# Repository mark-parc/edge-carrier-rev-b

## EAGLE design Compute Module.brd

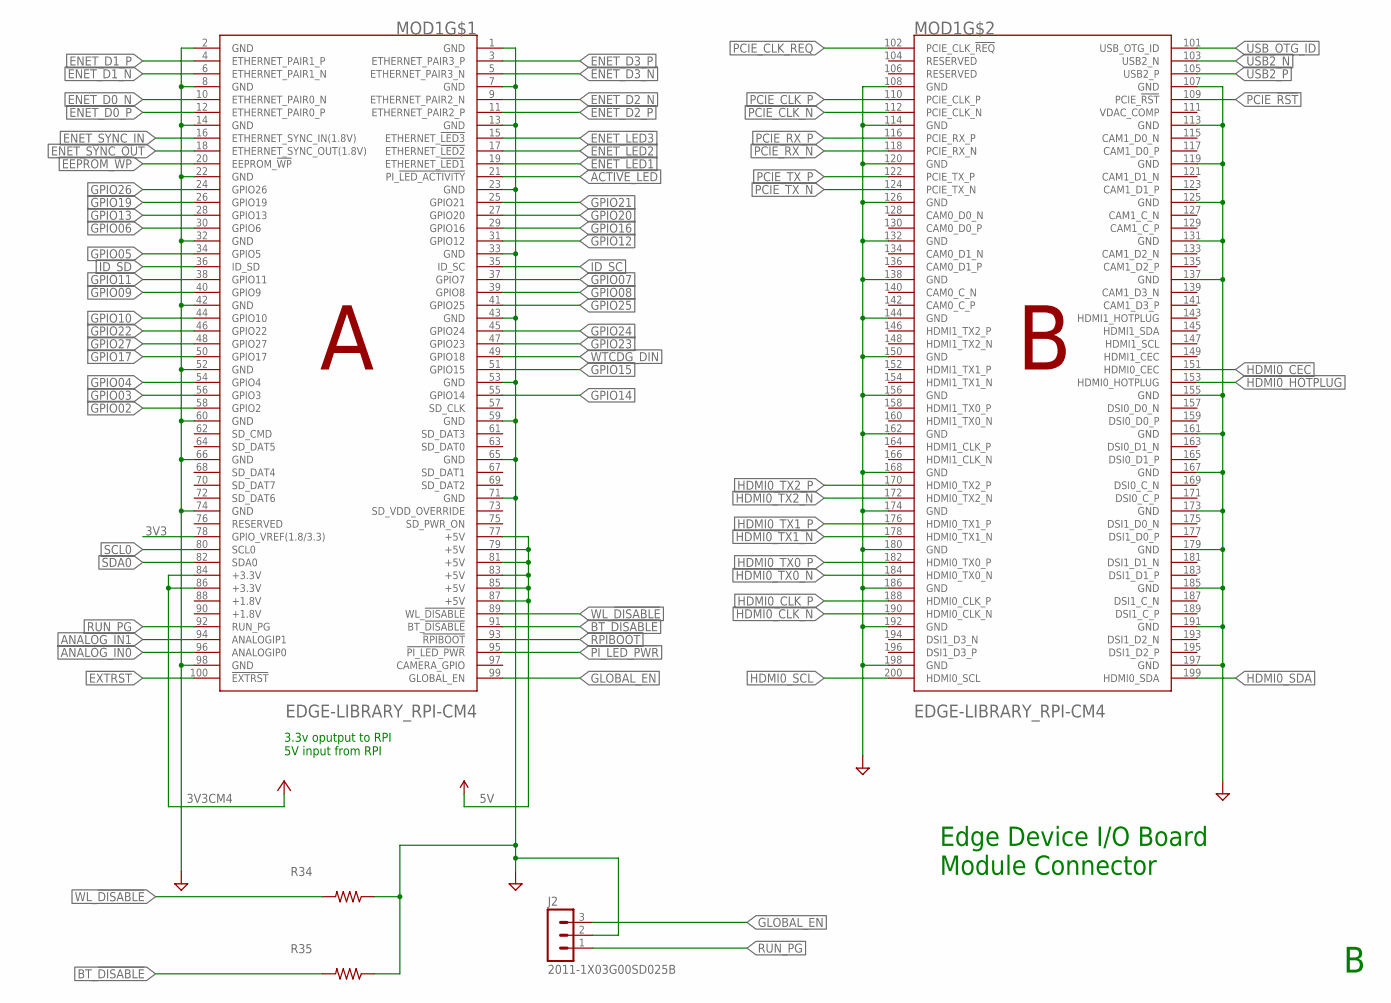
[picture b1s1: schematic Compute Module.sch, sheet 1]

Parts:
J2: 2011-1X03G00SD025B; CON-LSTB_MA03-1; MPN 2011-1X03G00SB; DIGIKEY 2553-2011-1X03G00SB-ND
MOD1: EDGE-LIBRARY_RPI-CM4
R34, R35: EDGE-LIBRARY_0805; MPN RC0805JR-070RL; DIGIKEY 311-0.0ARCT-ND

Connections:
3V3: MOD1.78 (GPIO_VREF(1.8/3.3)); also elsewhere on the board
3V3CM4: MOD1.84 (+3.3V), MOD1.86 (+3.3V)
5V: MOD1.77 (+5V), MOD1.79 (+5V), MOD1.81 (+5V), MOD1.83 (+5V), MOD1.85 (+5V), MOD1.87 (+5V); also elsewhere on the board
!EXTRST: MOD1.100 (!EXTRST); also elsewhere on the board
!PI_LED_PWR: MOD1.95 (!PI_LED_PWR); also elsewhere on the board
!RPIBOOT: MOD1.93 (!RPIBOOT); also elsewhere on the board
ACTIVE_!LED: MOD1.21 (PI_!LED_ACTIVITY); also elsewhere on the board
ANALOG_IN0: MOD1.96 (ANALOGIP0); also elsewhere on the board
ANALOG_IN1: MOD1.94 (ANALOGIP1); also elsewhere on the board
BT_!DISABLE: MOD1.91 (BT_!DISABLE), R35.2
EEPROM_!WP: MOD1.20 (EEPROM_!WP); also elsewhere on the board
ENET_!LED1: MOD1.19 (ETHERNET_!LED1); also elsewhere on the board
ENET_!LED2: MOD1.17 (ETHERNET_!LED2); also elsewhere on the board
ENET_!LED3: MOD1.15 (ETHERNET_!LED3); also elsewhere on the board
ENET_D0_N: MOD1.10 (ETHERNET_PAIR0_N); also elsewhere on the board
ENET_D0_P: MOD1.12 (ETHERNET_PAIR0_P); also elsewhere on the board
ENET_D1_N: MOD1.6 (ETHERNET_PAIR1_N); also elsewhere on the board
ENET_D1_P: MOD1.4 (ETHERNET_PAIR1_P); also elsewhere on the board
ENET_D2_N: MOD1.9 (ETHERNET_PAIR2_N); also elsewhere on the board
ENET_D2_P: MOD1.11 (ETHERNET_PAIR2_P); also elsewhere on the board
ENET_D3_N: MOD1.5 (ETHERNET_PAIR3_N); also elsewhere on the board
ENET_D3_P: MOD1.3 (ETHERNET_PAIR3_P); also elsewhere on the board
ENET_SYNC_IN: MOD1.16 (ETHERNET_SYNC_IN(1.8V)); also elsewhere on the board
ENET_SYNC_OUT: MOD1.18 (ETHERNET_SYNC_OUT(1.8V)); also elsewhere on the board
GLOBAL_EN: J2.3, MOD1.99 (GLOBAL_EN); also elsewhere on the board
GND: J2.2, MOD1.1 (GND), MOD1.2 (GND), MOD1.7 (GND), MOD1.8 (GND), MOD1.13 (GND), MOD1.14 (GND), MOD1.22 (GND), MOD1.23 (GND), MOD1.32 (GND), MOD1.33 (GND), MOD1.42 (GND), MOD1.43 (GND), MOD1.52 (GND), MOD1.53 (GND), MOD1.59 (GND), MOD1.60 (GND), MOD1.65 (GND), MOD1.66 (GND), MOD1.71 (GND), MOD1.74 (GND), MOD1.98 (GND), MOD1.107 (GND), MOD1.108 (GND), MOD1.113 (GND), MOD1.114 (GND), MOD1.119 (GND), MOD1.120 (GND), MOD1.125 (GND), MOD1.126 (GND), MOD1.131 (GND), MOD1.132 (GND), MOD1.137 (GND), MOD1.138 (GND), MOD1.144 (GND), MOD1.150 (GND), MOD1.155 (GND), MOD1.156 (GND), MOD1.161 (GND), MOD1.162 (GND), MOD1.167 (GND), MOD1.168 (GND), MOD1.173 (GND), MOD1.174 (GND), MOD1.179 (GND), MOD1.180 (GND), MOD1.185 (GND), MOD1.186 (GND), MOD1.191 (GND), MOD1.192 (GND), MOD1.197 (GND), MOD1.198 (GND), R34.1, R35.1; also elsewhere on the board
GPIO02: MOD1.58 (GPIO2); also elsewhere on the board
GPIO03: MOD1.56 (GPIO3); also elsewhere on the board
GPIO04: MOD1.54 (GPIO4); also elsewhere on the board
GPIO05: MOD1.34 (GPIO5); also elsewhere on the board
GPIO06: MOD1.30 (GPIO6); also elsewhere on the board
GPIO07: MOD1.37 (GPIO7); also elsewhere on the board
GPIO08: MOD1.39 (GPIO8); also elsewhere on the board
GPIO09: MOD1.40 (GPIO9); also elsewhere on the board
GPIO10: MOD1.44 (GPIO10); also elsewhere on the board
GPIO11: MOD1.38 (GPIO11); also elsewhere on the board
GPIO12: MOD1.31 (GPIO12); also elsewhere on the board
GPIO13: MOD1.28 (GPIO13); also elsewhere on the board
GPIO14: MOD1.55 (GPIO14); also elsewhere on the board
GPIO15: MOD1.51 (GPIO15); also elsewhere on the board
GPIO16: MOD1.29 (GPIO16); also elsewhere on the board
GPIO17: MOD1.50 (GPIO17); also elsewhere on the board
GPIO19: MOD1.26 (GPIO19); also elsewhere on the board
GPIO20: MOD1.27 (GPIO20); also elsewhere on the board
GPIO21: MOD1.25 (GPIO21); also elsewhere on the board
GPIO22: MOD1.46 (GPIO22); also elsewhere on the board
GPIO23: MOD1.47 (GPIO23); also elsewhere on the board
GPIO24: MOD1.45 (GPIO24); also elsewhere on the board
GPIO25: MOD1.41 (GPIO25); also elsewhere on the board
GPIO26: MOD1.24 (GPIO26); also elsewhere on the board
GPIO27: MOD1.48 (GPIO27); also elsewhere on the board
HDMI0_CEC: MOD1.151 (HDMI0_CEC); also elsewhere on the board
HDMI0_CLK_N: MOD1.190 (HDMI0_CLK_N); also elsewhere on the board
HDMI0_CLK_P: MOD1.188 (HDMI0_CLK_P); also elsewhere on the board
HDMI0_HOTPLUG: MOD1.153 (HDMI0_HOTPLUG); also elsewhere on the board
HDMI0_SCL: MOD1.200 (HDMI0_SCL); also elsewhere on the board
HDMI0_SDA: MOD1.199 (HDMI0_SDA); also elsewhere on the board
HDMI0_TX0_N: MOD1.184 (HDMI0_TX0_N); also elsewhere on the board
HDMI0_TX0_P: MOD1.182 (HDMI0_TX0_P); also elsewhere on the board
HDMI0_TX1_N: MOD1.178 (HDMI0_TX1_N); also elsewhere on the board
HDMI0_TX1_P: MOD1.176 (HDMI0_TX1_P); also elsewhere on the board
HDMI0_TX2_N: MOD1.172 (HDMI0_TX2_N); also elsewhere on the board
HDMI0_TX2_P: MOD1.170 (HDMI0_TX2_P); also elsewhere on the board
ID_SC: MOD1.35 (ID_SC); also elsewhere on the board
ID_SD: MOD1.36 (ID_SD); also elsewhere on the board
PCIE_!RST: MOD1.109 (PCIE_!RST); also elsewhere on the board
PCIE_CLK_!REQ: MOD1.102 (PCIE_CLK_!REQ); also elsewhere on the board
PCIE_CLK_N: MOD1.112 (PCIE_CLK_N); also elsewhere on the board
PCIE_CLK_P: MOD1.110 (PCIE_CLK_P); also elsewhere on the board
PCIE_RX_N: MOD1.118 (PCIE_RX_N); also elsewhere on the board
PCIE_RX_P: MOD1.116 (PCIE_RX_P); also elsewhere on the board
PCIE_TX_N: MOD1.124 (PCIE_TX_N); also elsewhere on the board
PCIE_TX_P: MOD1.122 (PCIE_TX_P); also elsewhere on the board
RUN_PG: J2.1, MOD1.92 (RUN_PG); also elsewhere on the board
SCL0: MOD1.80 (SCL0); also elsewhere on the board
SDA0: MOD1.82 (SDA0); also elsewhere on the board
USB2_N: MOD1.103 (USB2_N); also elsewhere on the board
USB2_P: MOD1.105 (USB2_P); also elsewhere on the board
USB_OTG_ID: MOD1.101 (USB_OTG_ID); also elsewhere on the board
WL_!DISABLE: MOD1.89 (WL_!DISABLE), R34.2
WTCDG_DIN: MOD1.49 (GPIO18); also elsewhere on the board

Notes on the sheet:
Edge Device I/O Board Module Connector
3.3v oputput to RPI 5V input from RPI

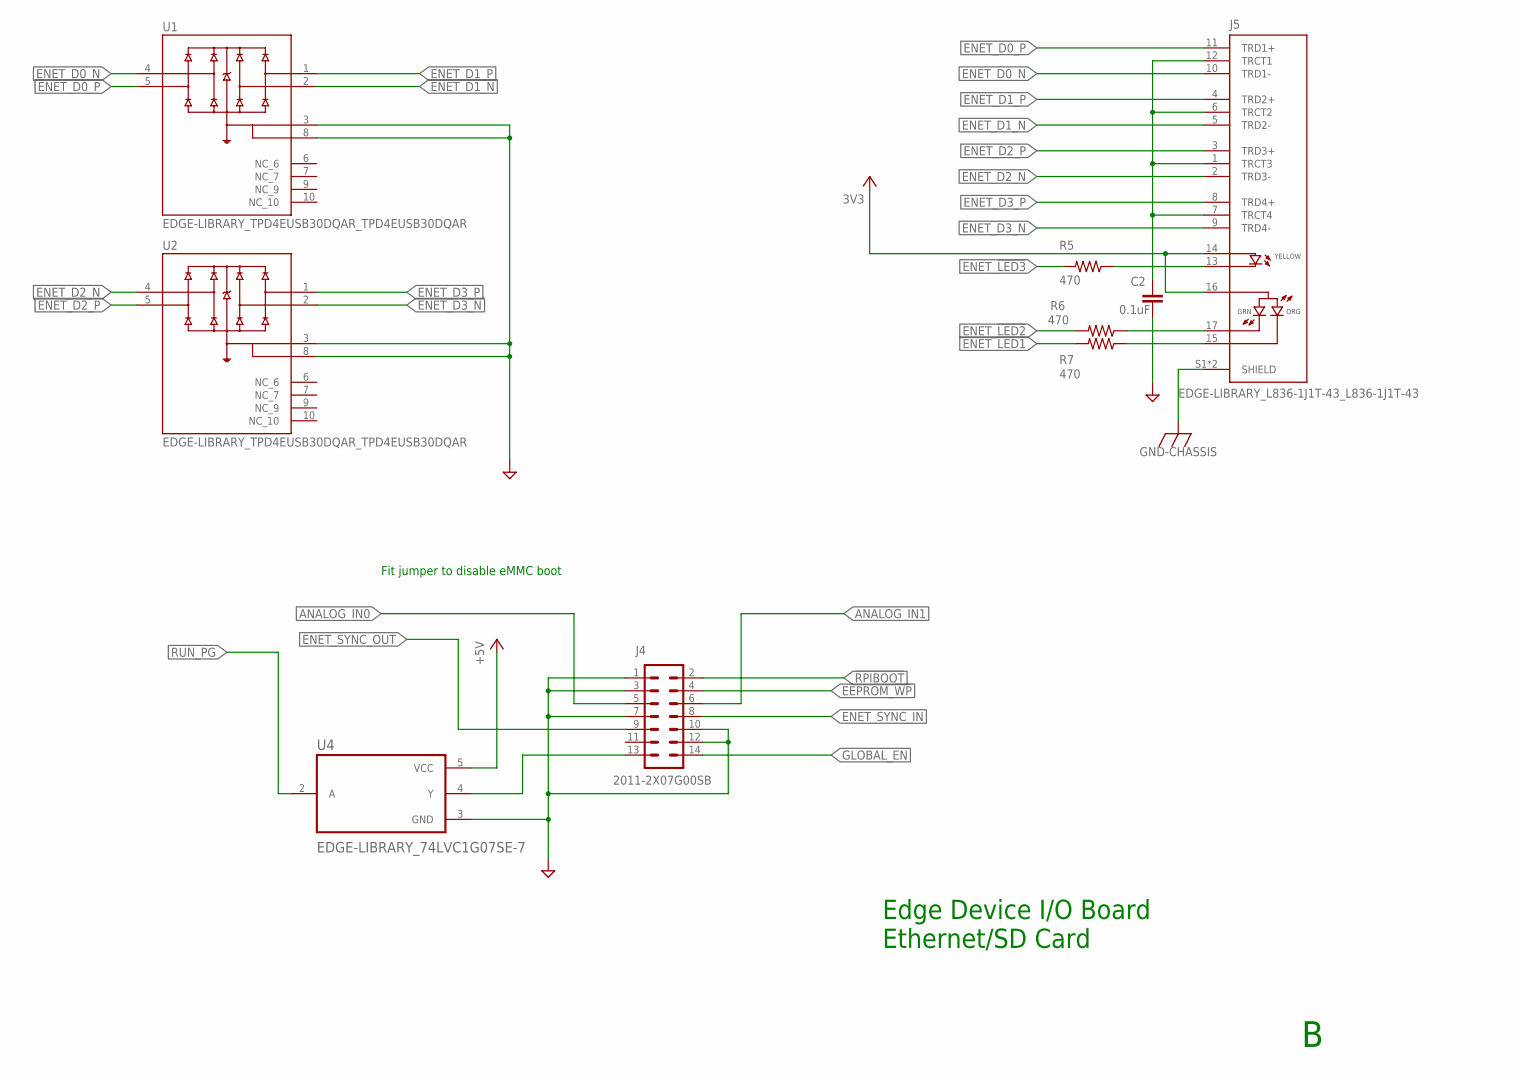
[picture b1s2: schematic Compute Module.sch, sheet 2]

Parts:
C2: 0.1uF; EDGE-LIBRARY_TUTORIAL---FUSION-360_CAPC1005X60; MPN C0402C104K4RACTU; DIGIKEY 399-3521-1-ND
J4: 2011-2X07G00SB; CON-LSTB_MA07-2; MPN 2011-2X07G00SB; DIGIKEY 2553-2011-2X07G00SB-ND
J5: EDGE-LIBRARY_L836-1J1T-43_L836-1J1T-43; EDGE-LIBRARY_L836-1J1T-43_BEL_L836-1J1T-43
R5, R6, R7: 470; EDGE-LIBRARY_TUTORIAL---FUSION-360_RESC1005X40; MPN RC0402FR-07470RL; DIGIKEY 311-470LRCT-ND
U1, U2: EDGE-LIBRARY_TPD4EUSB30DQAR_TPD4EUSB30DQAR; EDGE-LIBRARY_TPD4EUSB30DQAR_IC_TPD4EUSB30DQAR
U4: EDGE-LIBRARY_74LVC1G07SE-7; EDGE-LIBRARY_SOT65P210X110-5N

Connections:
3V3: J5.14, J5.16; also elsewhere on the board
5V: U4.5 (VCC); also elsewhere on the board
!RPIBOOT: J4.2; also elsewhere on the board
ANALOG_IN0: J4.5; also elsewhere on the board
ANALOG_IN1: J4.6; also elsewhere on the board
CGND: J5.S1 (SHIELD), J5.S2 (SHIELD); also elsewhere on the board
EEPROM_!WP: J4.4; also elsewhere on the board
ENET_!LED1: R7.2; also elsewhere on the board
ENET_!LED2: R6.2; also elsewhere on the board
ENET_!LED3: R5.2; also elsewhere on the board
ENET_D0_N: J5.10 (TRD1-), U1.4 (D2+); also elsewhere on the board
ENET_D0_P: J5.11 (TRD1+), U1.5 (D2-); also elsewhere on the board
ENET_D1_N: J5.5 (TRD2-), U1.2 (D1-); also elsewhere on the board
ENET_D1_P: J5.4 (TRD2+), U1.1 (D1+); also elsewhere on the board
ENET_D2_N: J5.2 (TRD3-), U2.4 (D2+); also elsewhere on the board
ENET_D2_P: J5.3 (TRD3+), U2.5 (D2-); also elsewhere on the board
ENET_D3_N: J5.9 (TRD4-), U2.2 (D1-); also elsewhere on the board
ENET_D3_P: J5.8 (TRD4+), U2.1 (D1+); also elsewhere on the board
ENET_SYNC_IN: J4.8; also elsewhere on the board
ENET_SYNC_OUT: J4.9; also elsewhere on the board
GLOBAL_EN: J4.14; also elsewhere on the board
GND: C2.2, J4.1, J4.3, J4.7, J4.10, J4.12, U1.3 (GND_3), U1.8 (GND_8), U2.3 (GND_3), U2.8 (GND_8), U4.3 (GND); also elsewhere on the board
unnamed: C2.1, J5.1 (TRCT3), J5.6 (TRCT2), J5.7 (TRCT4), J5.12 (TRCT1)
unnamed: J5.13, R5.1
unnamed: J5.17, R6.1
unnamed: J5.15, R7.1
unnamed: J4.13, U4.4 (Y)
RUN_PG: U4.2 (A); also elsewhere on the board

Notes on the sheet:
Edge Device I/O Board Ethernet/SD Card
Fit jumper to disable eMMC boot

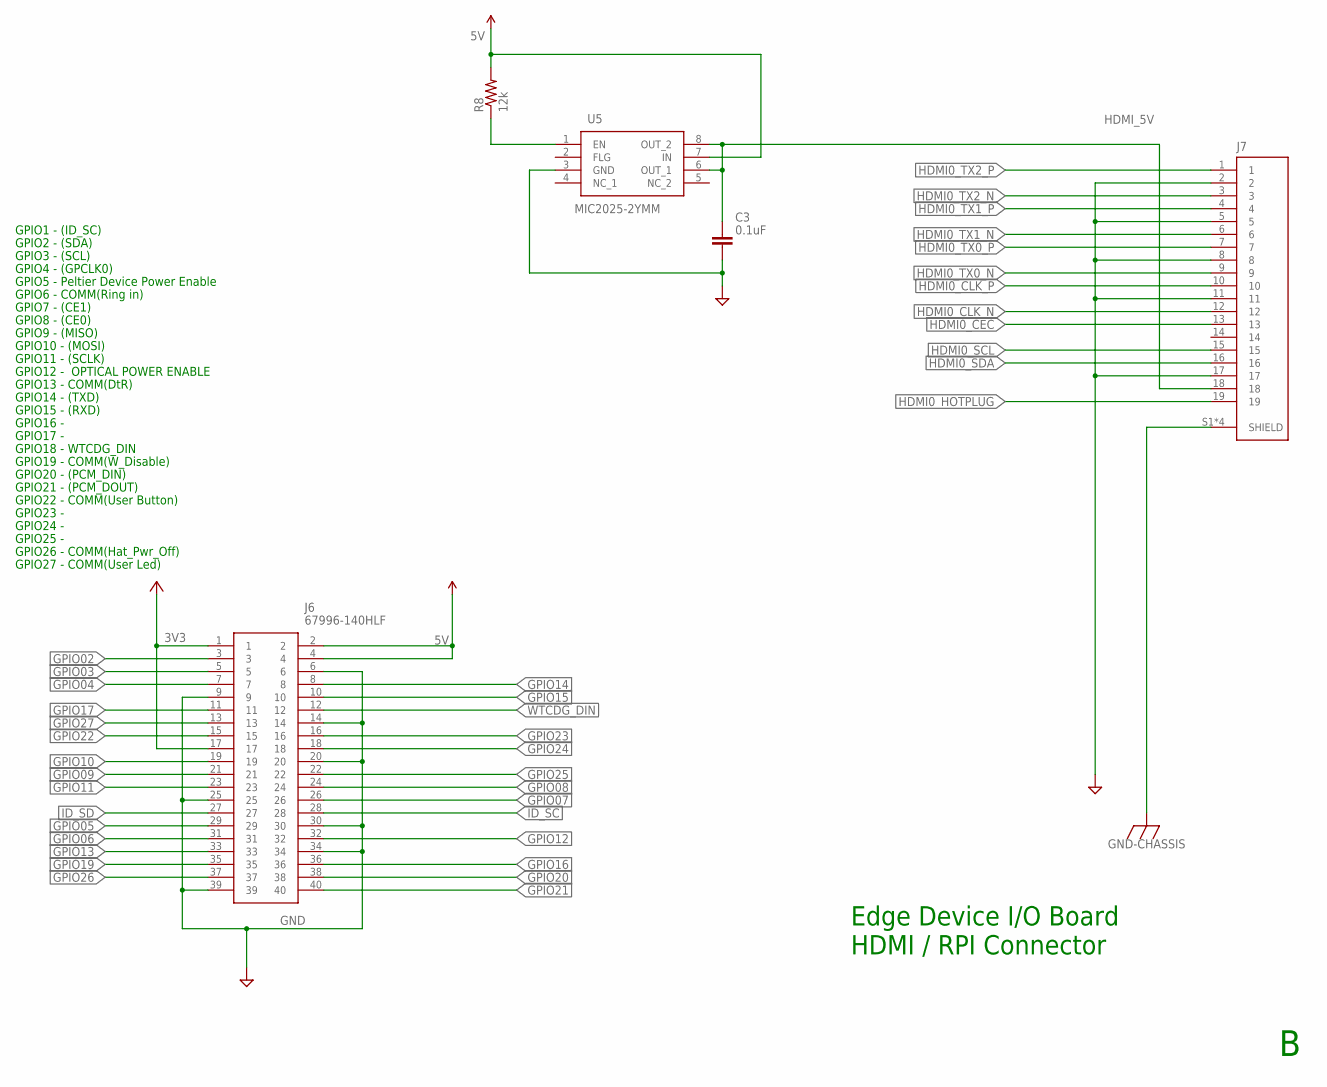
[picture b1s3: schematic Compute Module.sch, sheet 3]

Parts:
C3: 0.1uF; EDGE-LIBRARY_TUTORIAL---FUSION-360_CAPC1005X60; MPN C0402C104K4RACTU; DIGIKEY 399-3521-1-ND
J6: 67996-140HLF; HDRV40W67P254_2X20_5080X483X85
J7: EDGE-LIBRARY_HDMI_CONNECTOR_RT_SMA; EDGE-LIBRARY_STEWART_SS-53000-001
R8: 12k; EDGE-LIBRARY_TUTORIAL---FUSION-360_RESC1005X40; MPN RC0402FR-0712KL; DIGIKEY 311-12.0KLRCT-ND
U5: MIC2025-2YMM; SOP65P490X110-8N

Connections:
3V3: J6.1, J6.17; also elsewhere on the board
5V: J6.2, J6.4, R8.2, U5.7 (IN); also elsewhere on the board
CGND: J7.S1 (SHIELD), J7.S2 (SHIELD), J7.S3 (SHIELD), J7.S4 (SHIELD); also elsewhere on the board
GND: C3.2, J6.6, J6.9, J6.14, J6.20, J6.25, J6.30, J6.34, J6.39, J7.2, J7.5, J7.8, J7.11, J7.17, U5.3 (GND); also elsewhere on the board
GPIO02: J6.3; also elsewhere on the board
GPIO03: J6.5; also elsewhere on the board
GPIO04: J6.7; also elsewhere on the board
GPIO05: J6.29; also elsewhere on the board
GPIO06: J6.31; also elsewhere on the board
GPIO07: J6.26; also elsewhere on the board
GPIO08: J6.24; also elsewhere on the board
GPIO09: J6.21; also elsewhere on the board
GPIO10: J6.19; also elsewhere on the board
GPIO11: J6.23; also elsewhere on the board
GPIO12: J6.32; also elsewhere on the board
GPIO13: J6.33; also elsewhere on the board
GPIO14: J6.8; also elsewhere on the board
GPIO15: J6.10; also elsewhere on the board
GPIO16: J6.36; also elsewhere on the board
GPIO17: J6.11; also elsewhere on the board
GPIO19: J6.35; also elsewhere on the board
GPIO20: J6.38; also elsewhere on the board
GPIO21: J6.40; also elsewhere on the board
GPIO22: J6.15; also elsewhere on the board
GPIO23: J6.16; also elsewhere on the board
GPIO24: J6.18; also elsewhere on the board
GPIO25: J6.22; also elsewhere on the board
GPIO26: J6.37; also elsewhere on the board
GPIO27: J6.13; also elsewhere on the board
HDMI0_CEC: J7.13; also elsewhere on the board
HDMI0_CLK_N: J7.12; also elsewhere on the board
HDMI0_CLK_P: J7.10; also elsewhere on the board
HDMI0_HOTPLUG: J7.19; also elsewhere on the board
HDMI0_SCL: J7.15; also elsewhere on the board
HDMI0_SDA: J7.16; also elsewhere on the board
HDMI0_TX0_N: J7.9; also elsewhere on the board
HDMI0_TX0_P: J7.7; also elsewhere on the board
HDMI0_TX1_N: J7.6; also elsewhere on the board
HDMI0_TX1_P: J7.4; also elsewhere on the board
HDMI0_TX2_N: J7.3; also elsewhere on the board
HDMI0_TX2_P: J7.1; also elsewhere on the board
HDMI_5V: C3.1, J7.18, U5.6 (OUT_1), U5.8 (OUT_2)
ID_SC: J6.28; also elsewhere on the board
ID_SD: J6.27; also elsewhere on the board
unnamed: R8.1, U5.1 (EN)
WTCDG_DIN: J6.12; also elsewhere on the board

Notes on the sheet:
Edge Device I/O Board HDMI / RPI Connector
GPIO18 - WTCDG_DIN
GPIO27 - COMM(User Led)
GPIO22 - COMM(User Button)
GPIO6 - COMM(Ring in)
GPIO13 - COMM(DtR)
GPIO19 - COMM(W_Disable)
GPIO26 - COMM(Hat_Pwr_Off)
GPIO1 - (ID_SC)
GPIO2 - (SDA)
GPIO3 - (SCL)
GPIO4 - (GPCLK0)
GPIO5 - Peltier Device Power Enable
GPIO7 - (CE1)
GPIO8 - (CE0)
GPIO9 - (MISO)
GPIO10 - (MOSI)
GPIO11 - (SCLK)
GPIO12 - OPTICAL POWER ENABLE
GPIO14 - (TXD)
GPIO15 - (RXD)
GPIO16 -
GPIO17 -
GPIO20 - (PCM_DIN)
GPIO21 - (PCM_DOUT)
GPIO23 -
GPIO24 -
GPIO25 -

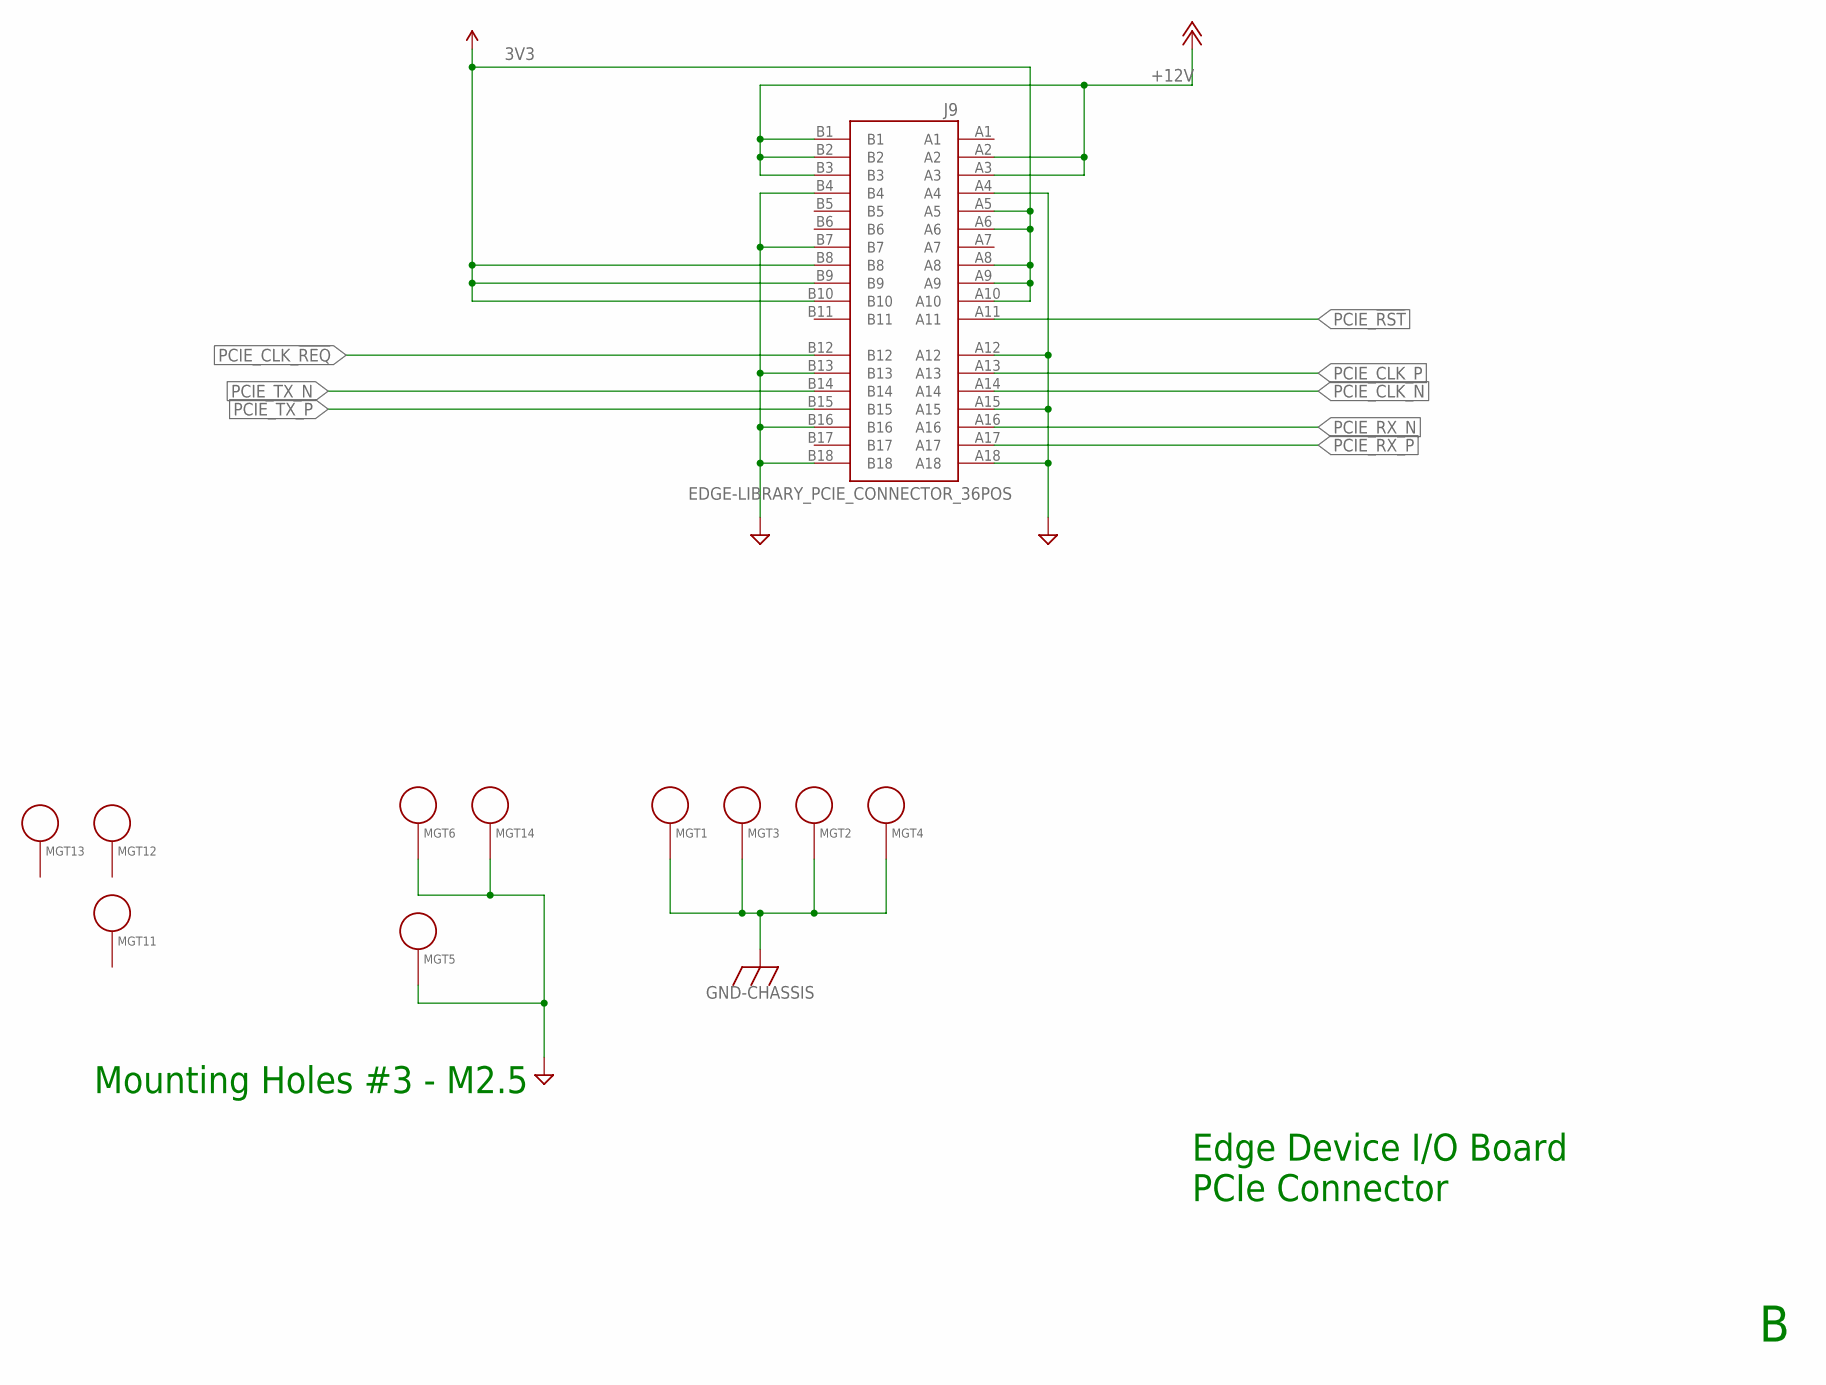
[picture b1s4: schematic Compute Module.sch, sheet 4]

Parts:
J9: EDGE-LIBRARY_PCIE_CONNECTOR_36POS; EDGE-LIBRARY_AMPHENOL_10018784-10210TLF
MGT1, MGT2, MGT3, MGT4, MGT5, MGT6, MGT14: MOUNTING_HOLE; BEAGLEBONEBLACK_MOUNTING_HOLE; DIGIKEY DNP
MGT11, MGT12, MGT13: MOUNTING_HOLE; BEAGLEBONEBLACK_MOUNTING_HOLE

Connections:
3V3: J9.A5, J9.A6, J9.A8, J9.A9, J9.A10, J9.B8, J9.B9, J9.B10; also elsewhere on the board
+12V: J9.A2, J9.A3, J9.B1, J9.B2, J9.B3; also elsewhere on the board
CGND: MGT1.P$1, MGT2.P$1, MGT3.P$1, MGT4.P$1; also elsewhere on the board
GND: J9.A4, J9.A12, J9.A15, J9.A18, J9.B4, J9.B7, J9.B13, J9.B16, J9.B18, MGT5.P$1, MGT6.P$1, MGT14.P$1; also elsewhere on the board
PCIE_!RST: J9.A11; also elsewhere on the board
PCIE_CLK_!REQ: J9.B12; also elsewhere on the board
PCIE_CLK_N: J9.A14; also elsewhere on the board
PCIE_CLK_P: J9.A13; also elsewhere on the board
PCIE_RX_N: J9.A16; also elsewhere on the board
PCIE_RX_P: J9.A17; also elsewhere on the board
PCIE_TX_N: J9.B14; also elsewhere on the board
PCIE_TX_P: J9.B15; also elsewhere on the board

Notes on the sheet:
Edge Device I/O Board PCIe Connector
Mounting Holes #3 - M2.5

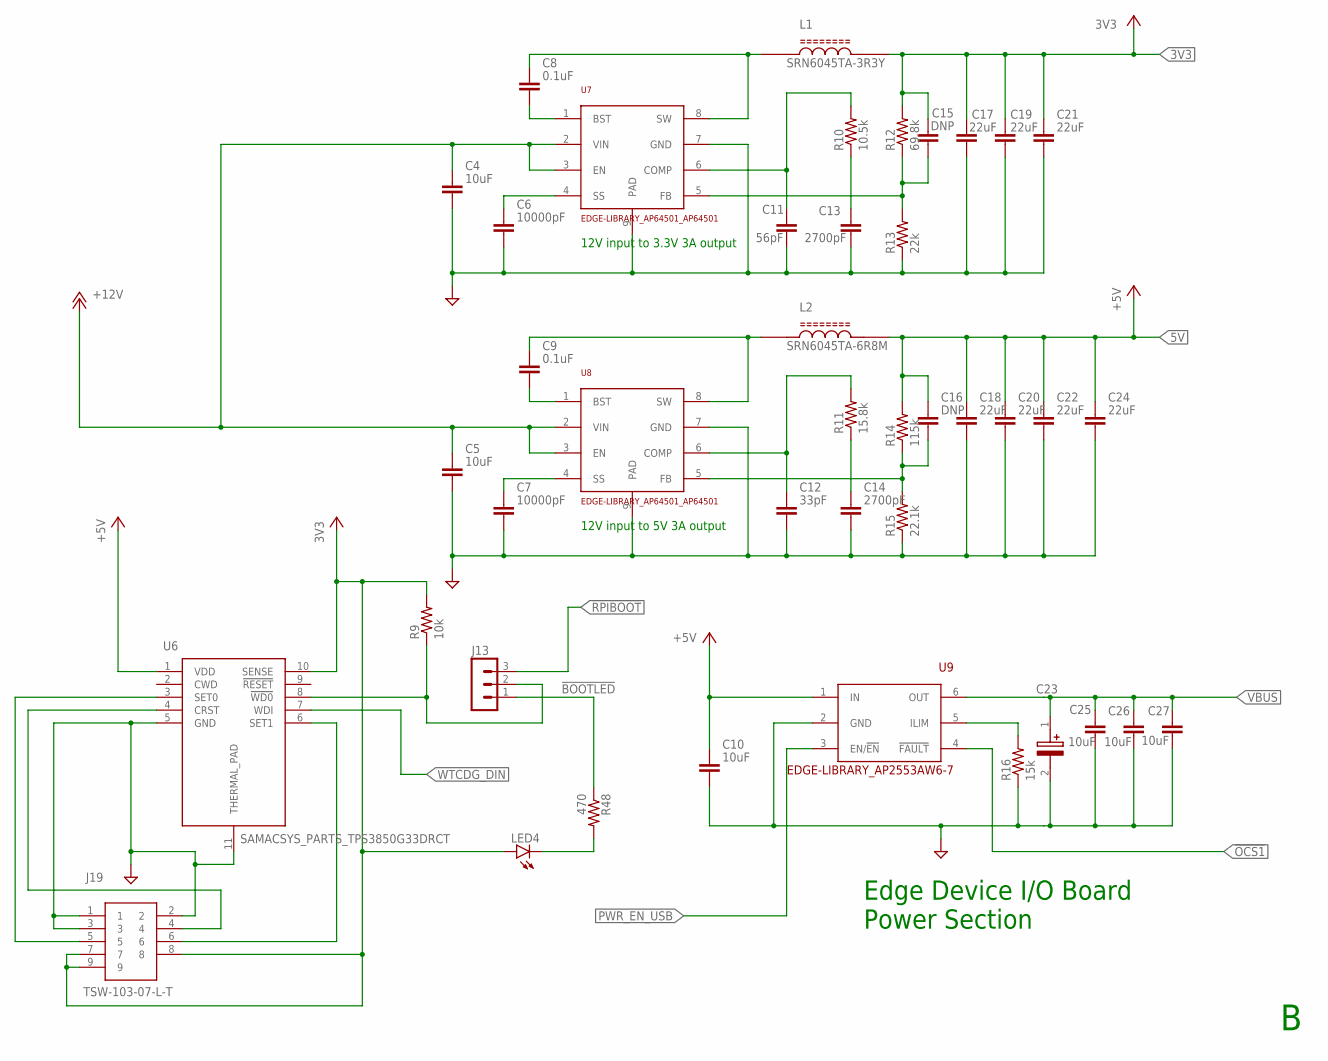
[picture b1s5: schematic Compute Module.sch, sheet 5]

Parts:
C4, C5, C10, C25, C26, C27: 10uF; EDGE-LIBRARY_TUTORIAL---FUSION-360_CAPC2012X110; MPN GRM21BR71A106KA73K; DIGIKEY 490-14381-1-ND
C6, C7: 10000pF; EDGE-LIBRARY_TUTORIAL---FUSION-360_CAPC1005X60; MPN CM02X5R103M16AH; DIGIKEY 1253-CM02X5R103M16AHCT-ND
C8, C9: 0.1uF; EDGE-LIBRARY_TUTORIAL---FUSION-360_CAPC1005X60; MPN C0402C104K4RACTU; DIGIKEY 399-3521-1-ND
C11: 56pF; EDGE-LIBRARY_TUTORIAL---FUSION-360_CAPC1005X60; MPN EMK042CG560JC-W; DIGIKEY 587-6134-1-ND
C12: 33pF; EDGE-LIBRARY_TUTORIAL---FUSION-360_CAPC1005X60; MPN GMC04CG330J16NT; DIGIKEY 2571-GMC04CG330J16NTTR-ND
C13, C14: 2700pF; EDGE-LIBRARY_TUTORIAL---FUSION-360_CAPC1005X60; MPN GMC04X5R272M50NT; DIGIKEY 2571-GMC04X5R272M50NTTR-ND
C15, C16: DNP; EDGE-LIBRARY_TUTORIAL---FUSION-360_CAPC1005X60
C17, C18, C19, C20, C21, C22, C24: 22uF; EDGE-LIBRARY_TUTORIAL---FUSION-360_CAPC1005X60; MPN GMC04X5R226M6R3NT; DIGIKEY 2571-GMC04X5R226M6R3NTTR-ND
C23: 100uF; CAPPM7343X200N
J13: 2553-2011-1X03G00SB-ND; CON-LSTB_MA03-1; MPN 2011-1X03G00SB; DIGIKEY 2553-2011-1X03G00SB-ND
J19: TSW-103-07-L-T; HDRV9W64P254_3X3_762X749X838P
L1: EDGE-LIBRARY_SRN6045TA-3R3Y_SRN6045TA-3R3Y; EDGE-LIBRARY_SRN6045TA-3R3Y_IND_SRN6045TA-3R3Y
L2: EDGE-LIBRARY_SRN6045TA-3R3Y_SRN6045TA-3R3Y; EDGE-LIBRARY_SRN6045TA-3R3Y_IND_SRN6045TA-3R3Y; MPN SRN6045TA-6R8M; DIGIKEY SRN6045TA-6R8MCT-ND
LED4: LTST-S270KGKT; LED_CHIP-LED0603; MPN LTST-S270KGKT; DIGIKEY LTST-S270KGKT
R9: 10k; EDGE-LIBRARY_TUTORIAL---FUSION-360_RESC1005X40; MPN RM04J103CT; DIGIKEY 2571-RM04J103CTTR-ND
R10: 10.5k; EDGE-LIBRARY_TUTORIAL---FUSION-360_RESC1005X40; MPN RC0402FR-0710K5L; DIGIKEY YAG2951CT-ND
R11: 15.8k; EDGE-LIBRARY_TUTORIAL---FUSION-360_RESC1005X40; MPN CRCW040215K8FKED; DIGIKEY 541-15.8KLCT-ND
R12: 69.8k; EDGE-LIBRARY_TUTORIAL---FUSION-360_RESC1005X40; MPN RMCF0402FT69K8; DIGIKEY RMCF0402FT69K8CT-ND
R13: 22k; EDGE-LIBRARY_TUTORIAL---FUSION-360_RESC1005X40; MPN RM04J223CT; DIGIKEY 2571-RM04J222CTTR-ND
R14: 115k; EDGE-LIBRARY_TUTORIAL---FUSION-360_RESC1005X40; MPN RP73PF1E115KBTD; DIGIKEY A127517CT-ND
R15: 22.1k; EDGE-LIBRARY_TUTORIAL---FUSION-360_RESC1005X40; MPN RN04D2212CT10-25; DIGIKEY 2571-RN04D2212CT10-25TR-ND
R16: 15k; EDGE-LIBRARY_TUTORIAL---FUSION-360_RESC1005X40; MPN RMCF0402FT15K0; DIGIKEY RMCF0402FT15K0CT-ND
R48: 470; EDGE-LIBRARY_TUTORIAL---FUSION-360_RESC1005X40; MPN RC0402FR-07470RL; DIGIKEY 311-470LRCT-ND
U6: SAMACSYS_PARTS_TPS3850G33DRCT; SAMACSYS_PARTS_SON50P300X300X100-11N; DIGIKEY 2156-TPS3850G33DRCR-ND
U7, U8: EDGE-LIBRARY_AP64501_AP64501; EDGE-LIBRARY_AP64501_SOIC127P600X265-9T261X350N
U9: EDGE-LIBRARY_AP2553AW6-7; EDGE-LIBRARY_SOT95P280X140-6N; MPN AP22653AW6-7; DIGIKEY 31-AP22653AW6-7CT-ND

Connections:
3V3: C15.1, C17.1, C19.1, C21.1, J19.7, J19.8, J19.9, L1.2, LED4.A, R9.2, R12.2, U6.10 (SENSE); also elsewhere on the board
5V: C10.1, C16.1, C18.1, C20.1, C22.1, C24.1, L2.2, R14.2, U6.1 (VDD), U9.1 (IN); also elsewhere on the board
!BOOTLED: J13.1, R48.1
!OCS1: U9.4 (!FAULT); also elsewhere on the board
!RPIBOOT: J13.3; also elsewhere on the board
+12V: C4.1, C5.1, U7.2 (VIN), U7.3 (EN), U8.2 (VIN), U8.3 (EN); also elsewhere on the board
GND: C4.2, C5.2, C6.2, C7.2, C10.2, C11.2, C12.2, C13.2, C14.2, C17.2, C18.2, C19.2, C20.2, C21.2, C22.2, C23.2 (-), C24.2, C25.2, C26.2, C27.2, J19.1, J19.2, J19.3, R13.1, R15.1, R16.1, U6.5 (GND), U6.11 (THERMAL_PAD), U7.7 (GND), U7.9 (PAD), U8.7 (GND), U8.9 (PAD), U9.2 (GND); also elsewhere on the board
unnamed: J19.6, U6.6 (SET1)
unnamed: C8.2, U7.1 (BST)
unnamed: C8.1, L1.1, U7.8 (SW)
unnamed: C6.1, U7.4 (SS)
unnamed: C11.1, R10.2, U7.6 (COMP)
unnamed: C13.1, R10.1
unnamed: C15.2, R12.1, R13.2, U7.5 (FB)
unnamed: R16.2, U9.5 (ILIM)
unnamed: C9.2, U8.1 (BST)
unnamed: C9.1, L2.1, U8.8 (SW)
unnamed: C7.1, U8.4 (SS)
unnamed: C12.1, R11.2, U8.6 (COMP)
unnamed: C14.1, R11.1
unnamed: C16.2, R14.1, R15.2, U8.5 (FB)
unnamed: J13.2, R9.1, U6.8 (!WD0)
unnamed: LED4.C, R48.2
unnamed: J19.5, U6.3 (SET0)
unnamed: J19.4, U6.4 (CRST)
PWR_EN_USB: U9.3 (EN/!EN); also elsewhere on the board
VBUS: C23.1 (+), C25.1, C26.1, C27.1, U9.6 (OUT); also elsewhere on the board
WTCDG_DIN: U6.7 (WDI); also elsewhere on the board

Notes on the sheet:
12V input to 3.3V 3A output
12V input to 5V 3A output
Edge Device I/O Board Power Section

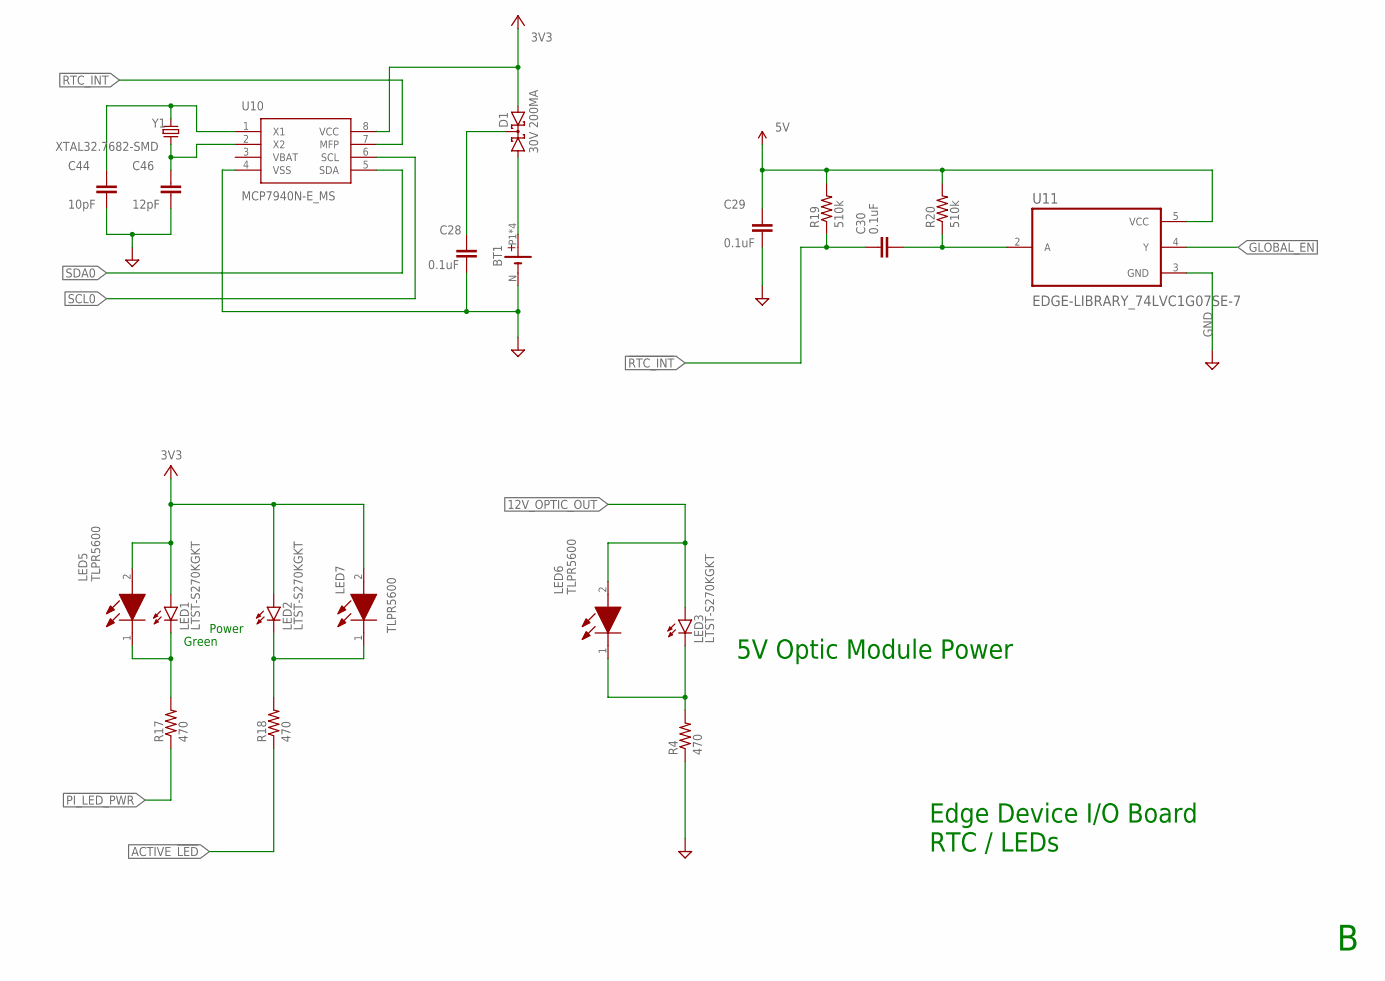
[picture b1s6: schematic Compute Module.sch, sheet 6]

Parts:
BT1: EDGE-LIBRARY_BATTERY_HOLDER; EDGE-LIBRARY_79523141
C28, C29, C30: 0.1uF; EDGE-LIBRARY_TUTORIAL---FUSION-360_CAPC1005X60; MPN C0402C104K4RACTU; DIGIKEY 399-3521-1-ND
C44: 10pF; EDGE-LIBRARY_TUTORIAL---FUSION-360_CAPC1005X60; MPN 478-04026D100JAT2ACT-ND; DIGIKEY 399-3521-1-ND
C46: 12pF; EDGE-LIBRARY_TUTORIAL---FUSION-360_CAPC1005X60; MPN 04026A120KAT2A; DIGIKEY 478-04026A120KAT2ACT-ND
D1: 30V 200MA; EDGE-LIBRARY_SOT23
LED1, LED2, LED3: LTST-S270KGKT; LED_CHIP-LED0603; MPN LTST-S270KGKT; DIGIKEY LTST-S270KGKT
LED5, LED6, LED7: TLPR5600; TLPP5600; DIGIKEY DNP
R4, R17, R18: 470; EDGE-LIBRARY_TUTORIAL---FUSION-360_RESC1005X40; MPN RC0402FR-07470RL; DIGIKEY 311-470LRCT-ND
R19, R20: 510k; EDGE-LIBRARY_TUTORIAL---FUSION-360_RESC1005X40; MPN RMCF0402JT510K; DIGIKEY RMCF0402JT510KCT-ND
U10: MCP7940N-E_MS; SOP65P490X110-8N
U11: EDGE-LIBRARY_74LVC1G07SE-7; EDGE-LIBRARY_SOT65P210X110-5N
Y1: XTAL32.7682-SMD; XTAL_ECS-.327-12.5-34R-TR; MPN QT3C-32.768KDZY-T; DIGIKEY 3003-QT3C-32.768KDZY-T-ND

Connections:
3V3: D1.2 (A2), LED1.A, LED2.A, LED5.2 (A), LED7.2 (A), U10.8 (VCC); also elsewhere on the board
5V: C29.1, R19.2, R20.2, U11.5 (VCC); also elsewhere on the board
12V_OPTIC_OUT: LED3.A, LED6.2 (A); also elsewhere on the board
!PI_LED_PWR: R17.1; also elsewhere on the board
!RTC_INT: C30.1, R19.1, U10.7 (MFP)
ACTIVE_!LED: R18.1; also elsewhere on the board
GLOBAL_EN: U11.4 (Y); also elsewhere on the board
GND: BT1.N (-), C28.2, C29.2, C44.2, C46.2, R4.1, U10.4 (VSS), U11.3 (GND); also elsewhere on the board
unnamed: C44.1, U10.1 (X1), Y1.2
unnamed: C46.1, U10.2 (X2), Y1.1
unnamed: C28.1, D1.3 (CC)
unnamed: BT1.P1 (+), BT1.P2 (+), BT1.P3 (+), BT1.P4 (+), D1.1 (A1)
unnamed: C30.2, R20.1, U11.2 (A)
unnamed: LED3.C, LED6.1 (K), R4.2
unnamed: LED1.C, LED5.1 (K), R17.2
unnamed: LED2.C, LED7.1 (K), R18.2
SCL0: U10.6 (SCL); also elsewhere on the board
SDA0: U10.5 (SDA); also elsewhere on the board

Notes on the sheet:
Edge Device I/O Board RTC / LEDs
Green
Power
5V Optic Module Power

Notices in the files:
Compute Module.brd:
All Rights Reserved
